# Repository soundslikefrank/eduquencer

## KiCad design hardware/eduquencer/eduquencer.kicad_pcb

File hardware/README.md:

# Eduquencer pcb schematic and design

## TODO

### Path to PCB prototype
- [ ] Finish the schematic
  - [x] Wire up rpi
  - [x] Add circuits for clock and reset
  - [x] Add debug header for flashing the rpi
  - [x] Add all the trigger jacks (+circuit around them, there might be some more resistors needed?)
  - [x] Add test-points for all i2c and SPI
  - [x] Check all GND in analog parts and change to GNDA (cv-in?)
  - [x] Annotate all parts
  - [x] Assign footprints (all footprints should be the kicad handsolder ones)
  - [ ] Add LED circuits for CV in (op-amps)
  - [ ] Adjust DAC opamp resistor for proper range (+add DAC out jack)
- [ ] Preliminary layout with all components (only footprint placement)
- [ ] Decide on a name
- [ ] Decide which jacks to use
- [ ] Do the final layout

## Preliminary BOM (per board)
- 1x RPI Pico (3,90)
- 3x https://www.digikey.de/de/products/detail/epcos-tdk-electronics/B72500D0160H060/1589537?s=N4IgTCBcDaIEIHYwFYAMqAiqCMA2VAEqviALoC%2BQA (1,5 @ 100)
- 1x GET AT JLC https://www.digikey.de/en/products/detail/texas-instruments/LM1117MP-5-0-NOPB/363590 (1,3 @ 25)
- 1x https://www.digikey.de/en/products/detail/analog-devices-inc/ADP150AUJZ-3-0-R7/2207488 (1 @ 25)
- 2x https://www.digikey.de/en/products/detail/microchip-technology/MCP23018-E-SS/1999506 (1,5 @ 25)
- 1x https://www.digikey.de/en/products/detail/texas-instruments/DAC80501MDGSR/11308813 (we probably want to get more) (5,6 @ 10)
- 2x 22u electrolytic cap (~0,5 total?)
- 9x XZM2CRK45WT-9 (red)
- 10x: XZDGK45WT-9 (green)
- 16x switches (~16 total?)
- 1x https://www.digikey.de/en/products/detail/texas-instruments/TL074CD/277422 (1 @ 25)
- 1x GET AT JLCPCB https://www.digikey.de/en/products/detail/microchip-technology/MCP6002-E-MS/683195 (0,4 @ 25)
- 1x https://www.digikey.com.au/en/products/detail/texas-instruments/OPA172IDR/4695363 (2,1 @ 25)
- 1x https://www.digikey.de/en/products/detail/texas-instruments/LM4040DIM3-10-0-NOPB/305141 (0,6 @ 25)
- 1x https://www.digikey.de/en/products/detail/texas-instruments/LM4040DIM3-5-0-NOPB/305140 (0,6 @ 25)
- 1x https://www.digikey.de/en/products/detail/panjit-international-inc/MMBT3904W-R1-00001/14660622 (0,15 @ 10)
- 3x GET AT JLC https://www.digikey.de/en/products/detail/diodes-incorporated/1N5819HWQ-7-F/10294862
- 1x GET AT JLC https://www.digikey.de/en/products/detail/panjit-international-inc/1N4148W-R1-00001/14660400
- 11x Thonkiconn (0,25 - I have ~300)
- 2x https://www.thonk.co.uk/shop/short-trimmer-pots/ B100K (0,8)

### LEDs
- MCP capabilities: 25mA sink per pin, 400mA total
- RPI capabilities: 3V3 is the main 3.3V supply to RP2040 and its I/O, generated by the on-board SMPS. This pin can be used to power external circuitry (maximum output current will depend on RP2040 load and VSYS voltage, it is recommended to keep the load on this pin less than 300mA).
- Step/channel LEDs:
  - Green: XZDGK45WT-9; 1.4mA@560Ω@3v3
  - Red: XZM2CRK45WT-9; 6.3mA@220Ω@3v3

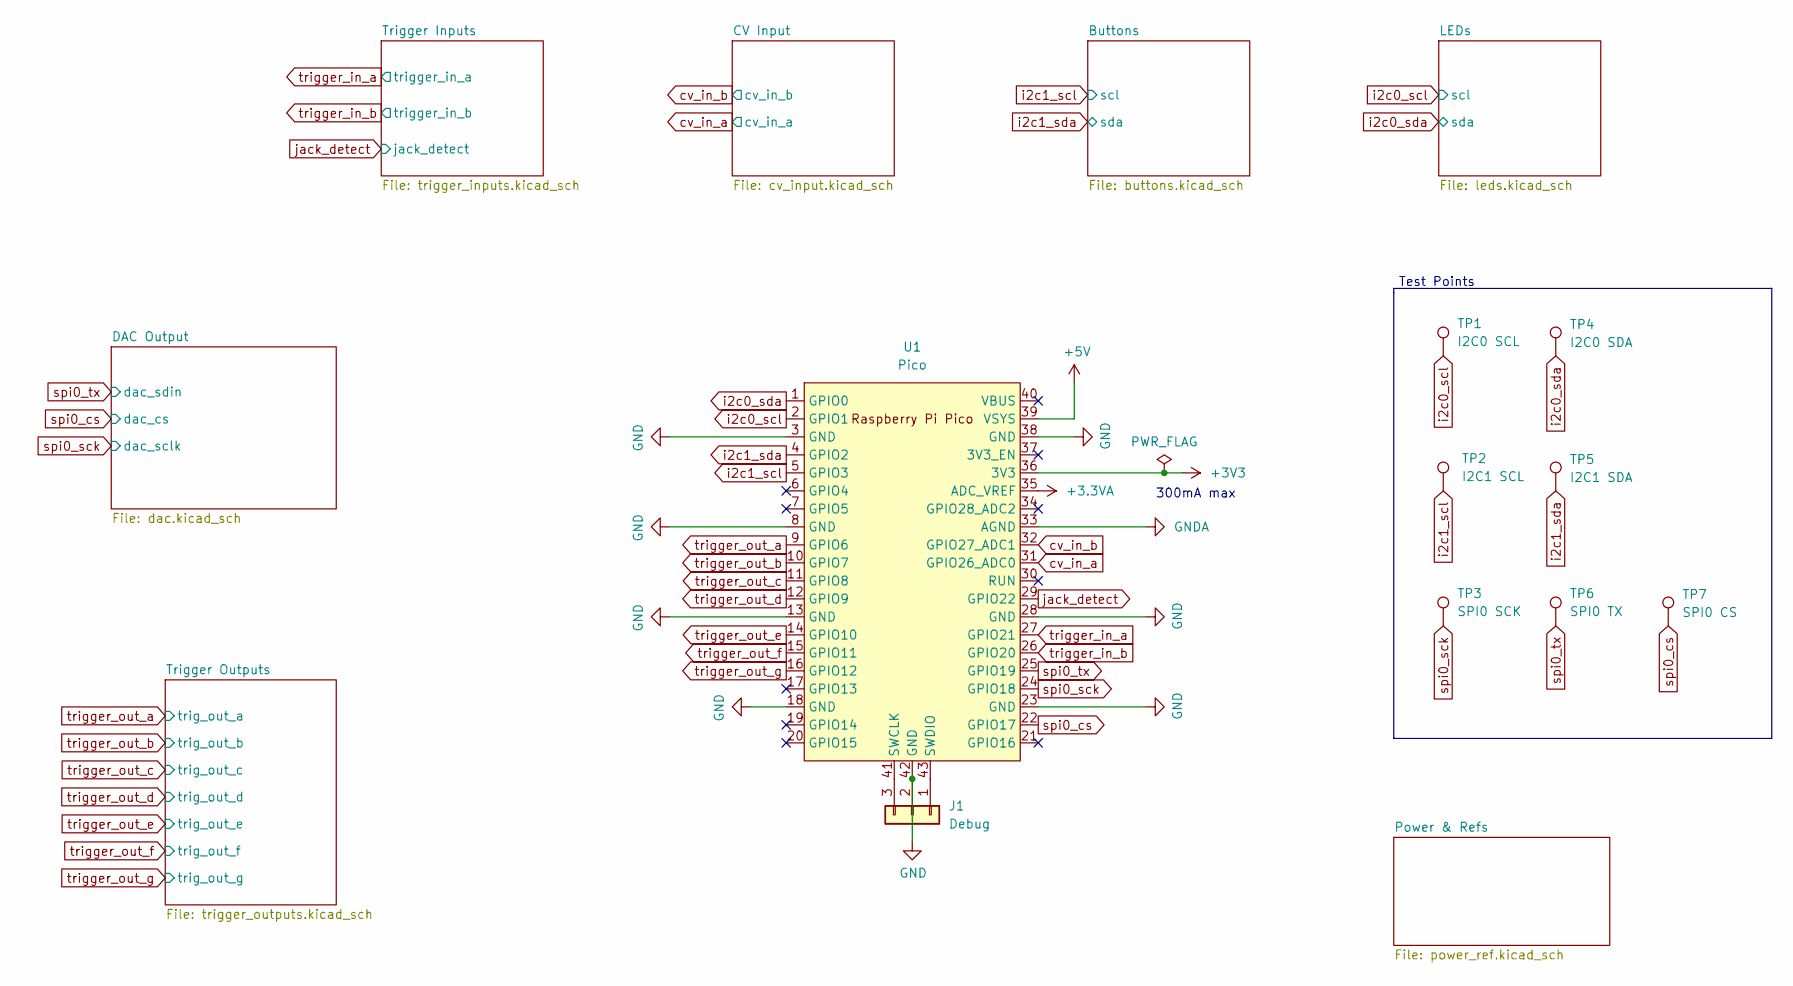
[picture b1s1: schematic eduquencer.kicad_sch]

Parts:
J1: Debug; PinHeader_1x03_P2.54mm_Vertical
TP1: I2C0 SCL; TestPoint_Pad_2.0x2.0mm
TP2: I2C1 SCL; TestPoint_Pad_2.0x2.0mm
TP3: SPI0 SCK; TestPoint_Pad_2.0x2.0mm
TP4: I2C0 SDA; TestPoint_Pad_2.0x2.0mm
TP5: I2C1 SDA; TestPoint_Pad_2.0x2.0mm
TP6: SPI0 TX; TestPoint_Pad_2.0x2.0mm
TP7: SPI0 CS; TestPoint_Pad_2.0x2.0mm
U1: Pico; RPi_Pico_SMD_TH

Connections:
+3.3VA: U1.35 (ADC_VREF); also elsewhere on the board
+5V: U1.39 (VSYS); also elsewhere on the board
GND: J1.2, U1.3 (GND), U1.8 (GND), U1.13 (GND), U1.18 (GND), U1.23 (GND), U1.28 (GND), U1.38 (GND), U1.42 (GND); also elsewhere on the board
GNDA: U1.33 (AGND); also elsewhere on the board
unnamed: J1.1, U1.43 (SWDIO)
unnamed: J1.3, U1.41 (SWCLK)
cv_in_a: U1.31 (GPIO26_ADC0); also elsewhere on the board
cv_in_b: U1.32 (GPIO27_ADC1); also elsewhere on the board
i2c0_scl: TP1.1, U1.2 (GPIO1); also elsewhere on the board
i2c0_sda: TP4.1, U1.1 (GPIO0); also elsewhere on the board
i2c1_scl: TP2.1, U1.5 (GPIO3); also elsewhere on the board
i2c1_sda: TP5.1, U1.4 (GPIO2); also elsewhere on the board
jack_detect: U1.29 (GPIO22); also elsewhere on the board
spi0_cs: TP7.1, U1.22 (GPIO17); also elsewhere on the board
spi0_sck: TP3.1, U1.24 (GPIO18); also elsewhere on the board
spi0_tx: TP6.1, U1.25 (GPIO19); also elsewhere on the board
trigger_in_a: U1.27 (GPIO21); also elsewhere on the board
trigger_in_b: U1.26 (GPIO20); also elsewhere on the board
trigger_out_a: U1.9 (GPIO6); also elsewhere on the board
trigger_out_b: U1.10 (GPIO7); also elsewhere on the board
trigger_out_c: U1.11 (GPIO8); also elsewhere on the board
trigger_out_d: U1.12 (GPIO9); also elsewhere on the board
trigger_out_e: U1.14 (GPIO10); also elsewhere on the board
trigger_out_f: U1.15 (GPIO11); also elsewhere on the board
trigger_out_g: U1.16 (GPIO12); also elsewhere on the board

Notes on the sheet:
300mA max
Test Points

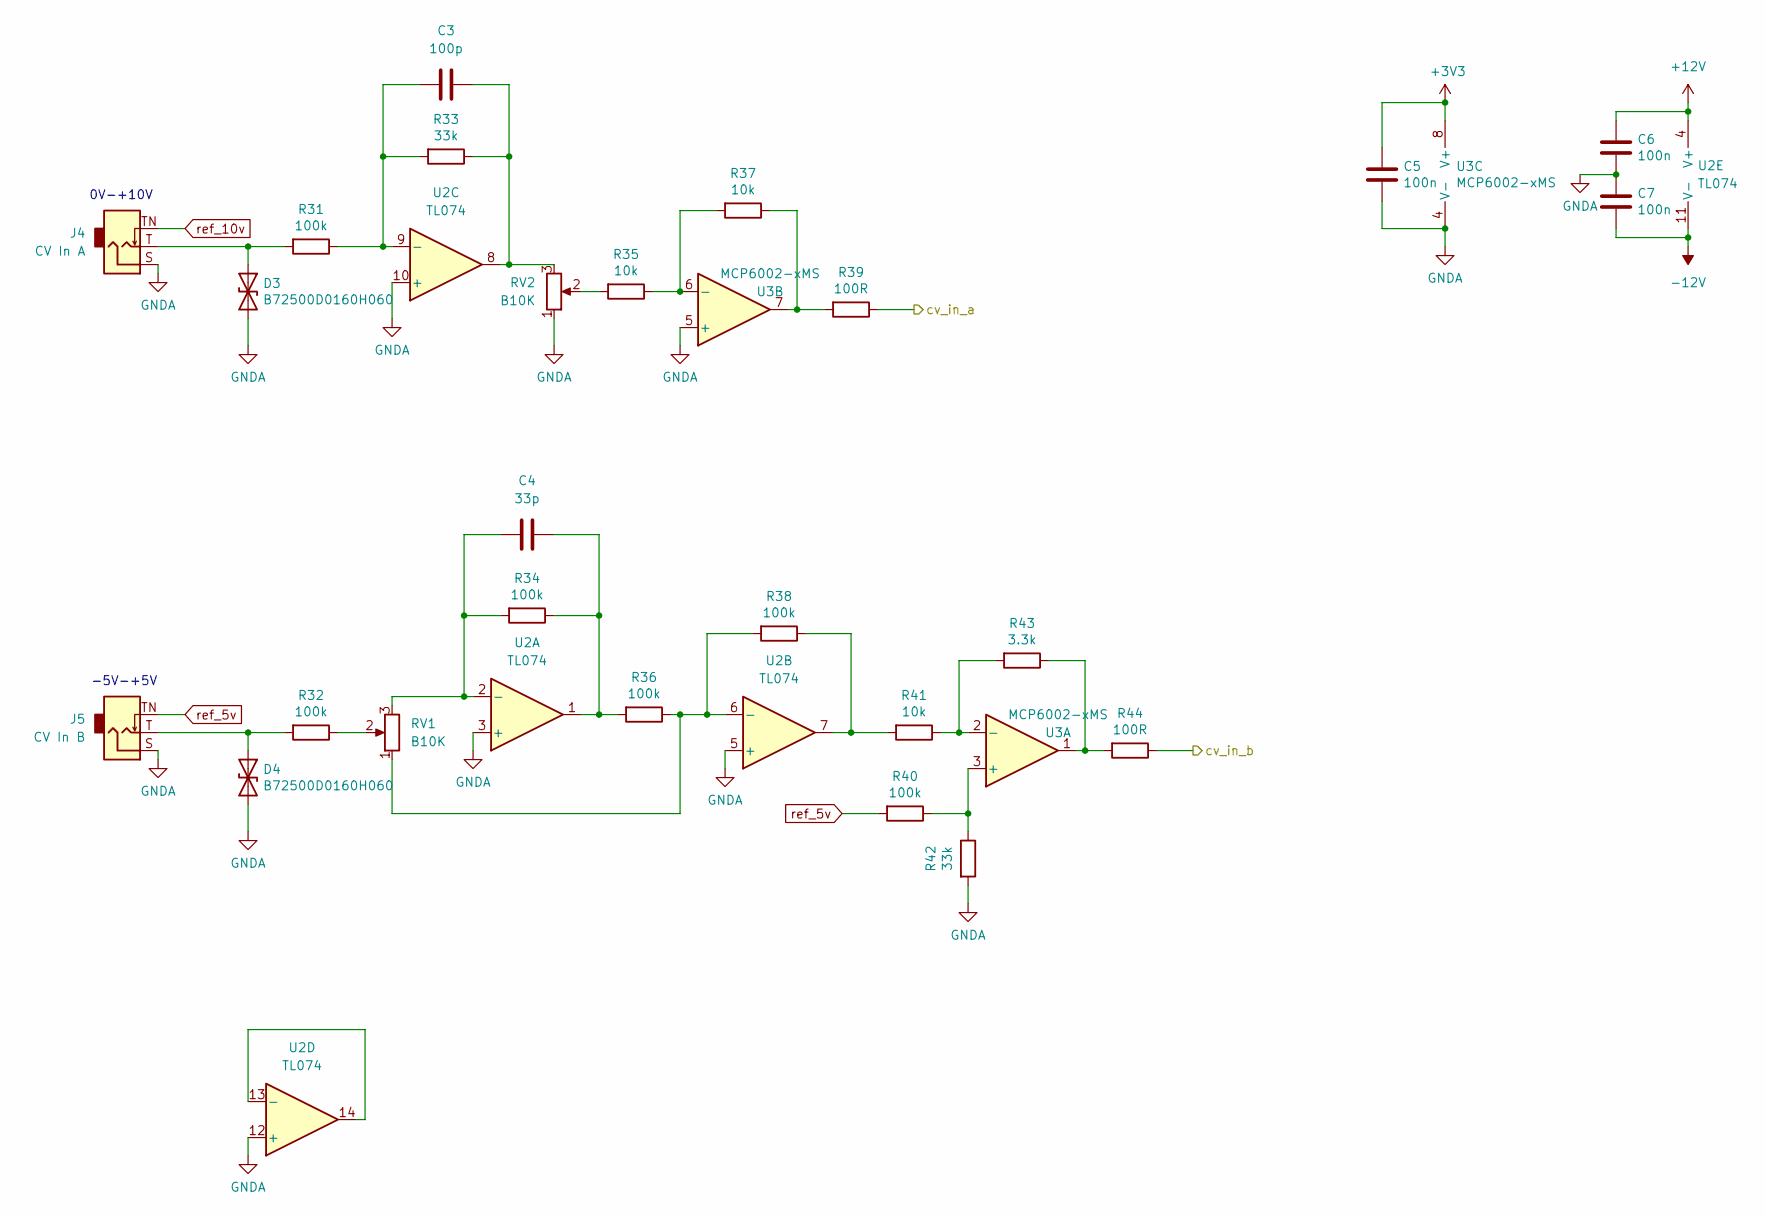
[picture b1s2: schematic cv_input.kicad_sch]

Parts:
C3: 100p; C_0603_1608Metric_Pad1.08x0.95mm_HandSolder
C4: 33p; C_0603_1608Metric_Pad1.08x0.95mm_HandSolder
C5, C6, C7: 100n; C_0603_1608Metric_Pad1.08x0.95mm_HandSolder
D3, D4: B72500D0160H060; D_0603_1608Metric_Pad1.05x0.95mm_HandSolder
J4: CV In A; Jack_3.5mm_QingPu_WQP-PJ301BM_Vertical
J5: CV In B; Jack_3.5mm_QingPu_WQP-PJ301BM_Vertical
R31, R32, R34, R36, R38, R40: 100k; R_0603_1608Metric_Pad0.98x0.95mm_HandSolder
R33, R42: 33k; R_0603_1608Metric_Pad0.98x0.95mm_HandSolder
R35, R37, R41: 10k; R_0603_1608Metric_Pad0.98x0.95mm_HandSolder
R39, R44: 100R; R_0603_1608Metric_Pad0.98x0.95mm_HandSolder
R43: 3.3k; R_0603_1608Metric_Pad0.98x0.95mm_HandSolder
RV1, RV2: B10K; Potentiometer_Alpha_RD901F-40-00D_Single_Vertical
U2: TL074; SOIC-14_3.9x8.7mm_P1.27mm
U3: MCP6002-xMS; SOIC-8_3.9x4.9mm_P1.27mm

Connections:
+12V: C6.1, U2.4 (V+); also elsewhere on the board
-12V: C7.2, U2.11 (V-); also elsewhere on the board
GNDA: C5.2, C6.2, C7.1, D3.2 (A2), D4.2 (A2), J4.S, J5.S, R42.2, RV2.1, U2.3 (+), U2.5 (+), U2.10 (+), U2.12 (+), U3.4 (V-), U3.5 (+); also elsewhere on the board
unnamed: C3.1, R31.1, R33.2, U2.9 (-)
unnamed: C3.2, R33.1, RV2.3, U2.8
unnamed: C4.1, R34.2, RV1.3, U2.2 (-)
unnamed: C4.2, R34.1, R36.2, U2.1
unnamed: D3.1 (A1), J4.T, R31.2
unnamed: D4.1 (A1), J5.T, R32.2
unnamed: R32.1, RV1.2
unnamed: R35.1, R37.2, U3.6 (-)
unnamed: R35.2, RV2.2
unnamed: R36.1, R38.2, RV1.1, U2.6 (-)
unnamed: R37.1, R39.2, U3.7
unnamed: R38.1, R41.2, U2.7
unnamed: R40.1, R42.1, U3.3 (+)
unnamed: R41.1, R43.2, U3.2 (-)
unnamed: R43.1, R44.2, U3.1
unnamed: U2.13 (-), U2.14
cv_in_a: R39.1; also elsewhere on the board
cv_in_b: R44.1; also elsewhere on the board
ref_5v: J5.TN, R40.2; also elsewhere on the board
ref_10v: J4.TN; also elsewhere on the board

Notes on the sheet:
0V-+10V
-5V-+5V

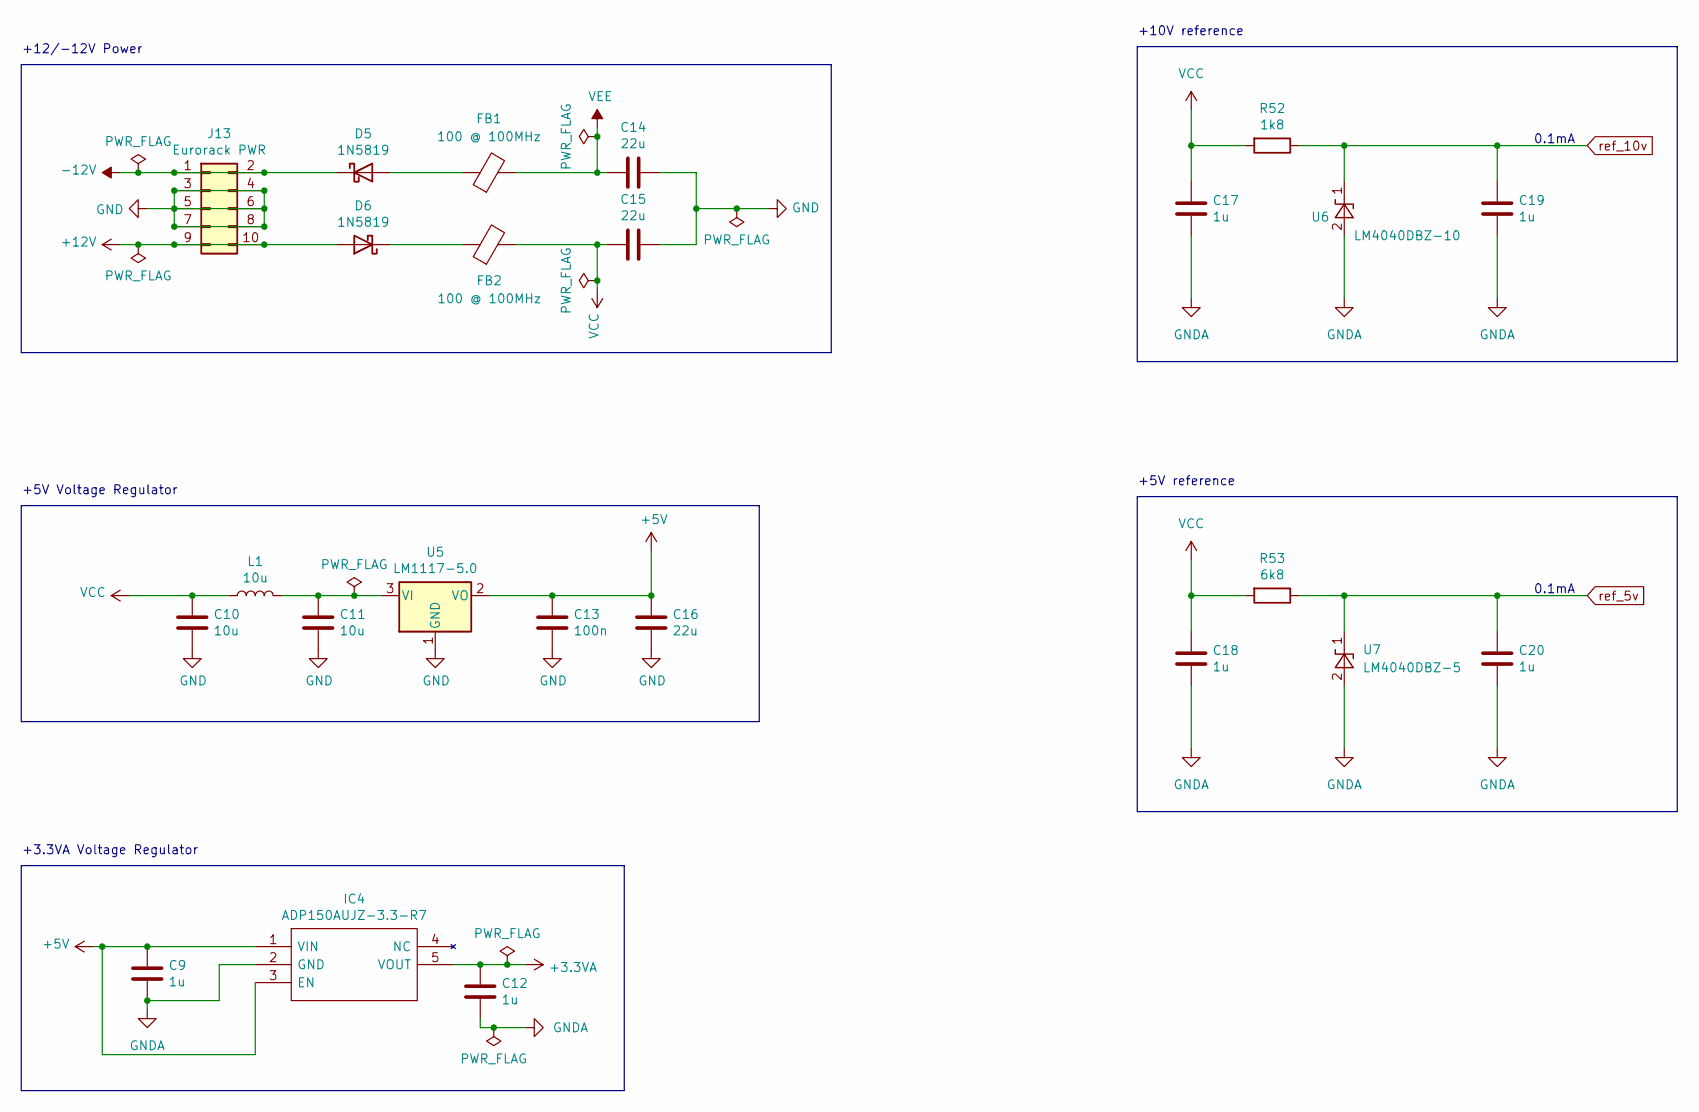
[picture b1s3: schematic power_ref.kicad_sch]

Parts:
C9, C12, C17, C18, C19, C20: 1u; C_0603_1608Metric_Pad1.08x0.95mm_HandSolder
C10, C11: 10u; C_0805_2012Metric_Pad1.18x1.45mm_HandSolder
C13: 100n; C_0603_1608Metric_Pad1.08x0.95mm_HandSolder
C14, C15: 22u; CP_Elec_5x5.3
C16: 22u; C_0805_2012Metric_Pad1.18x1.45mm_HandSolder
D5, D6: 1N5819; D_SOD-123
FB1, FB2: 100 @ 100MHz; L_0805_2012Metric_Pad1.05x1.20mm_HandSolder
IC4: ADP150AUJZ-3.3-R7; SOT95P280X100-5N; Manufacturer_Part_Number ADP150AUJZ-3.3-R7; Mouser Part Number 584-ADP150AUJZ-3.3R7
J13: Eurorack PWR; PinHeader_2x05_P2.54mm_Vertical_SMD
L1: 10u; L_0805_2012Metric_Pad1.05x1.20mm_HandSolder
R52: 1k8; R_0603_1608Metric_Pad0.98x0.95mm_HandSolder
R53: 6k8; R_0603_1608Metric_Pad0.98x0.95mm_HandSolder
U5: LM1117-5.0; SOT-223
U6: LM4040DBZ-10; SOT-23_Handsoldering
U7: LM4040DBZ-5; SOT-23_Handsoldering

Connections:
+3.3VA: C12.1, IC4.5 (VOUT); also elsewhere on the board
+5V: C9.1, C13.1, C16.2, IC4.1 (VIN), IC4.3 (EN), U5.2 (VO); also elsewhere on the board
+12V: D6.2 (A), J13.9, J13.10; also elsewhere on the board
-12V: D5.1 (K), J13.1, J13.2; also elsewhere on the board
GND: C10.2, C11.1, C13.2, C14.1, C15.1, C16.1, J13.3, J13.4, J13.5, J13.6, J13.7, J13.8, U5.1 (GND); also elsewhere on the board
GNDA: C9.2, C12.2, C17.2, C18.2, C19.2, C20.2, IC4.2 (GND), U6.2 (A), U7.2 (A); also elsewhere on the board
unnamed: C11.2, L1.2, U5.3 (VI)
unnamed: D5.2 (A), FB1.1
unnamed: D6.1 (K), FB2.1
VCC: C10.1, C15.2, C17.1, C18.1, FB2.2, L1.1, R52.2, R53.2; also elsewhere on the board
VEE: C14.2, FB1.2; also elsewhere on the board
ref_5v: C20.1, R53.1, U7.1 (K); also elsewhere on the board
ref_10v: C19.1, R52.1, U6.1 (K); also elsewhere on the board

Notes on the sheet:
+5V Voltage Regulator
0.1mA
+3.3VA Voltage Regulator
+12/-12V Power
+10V reference
+5V reference

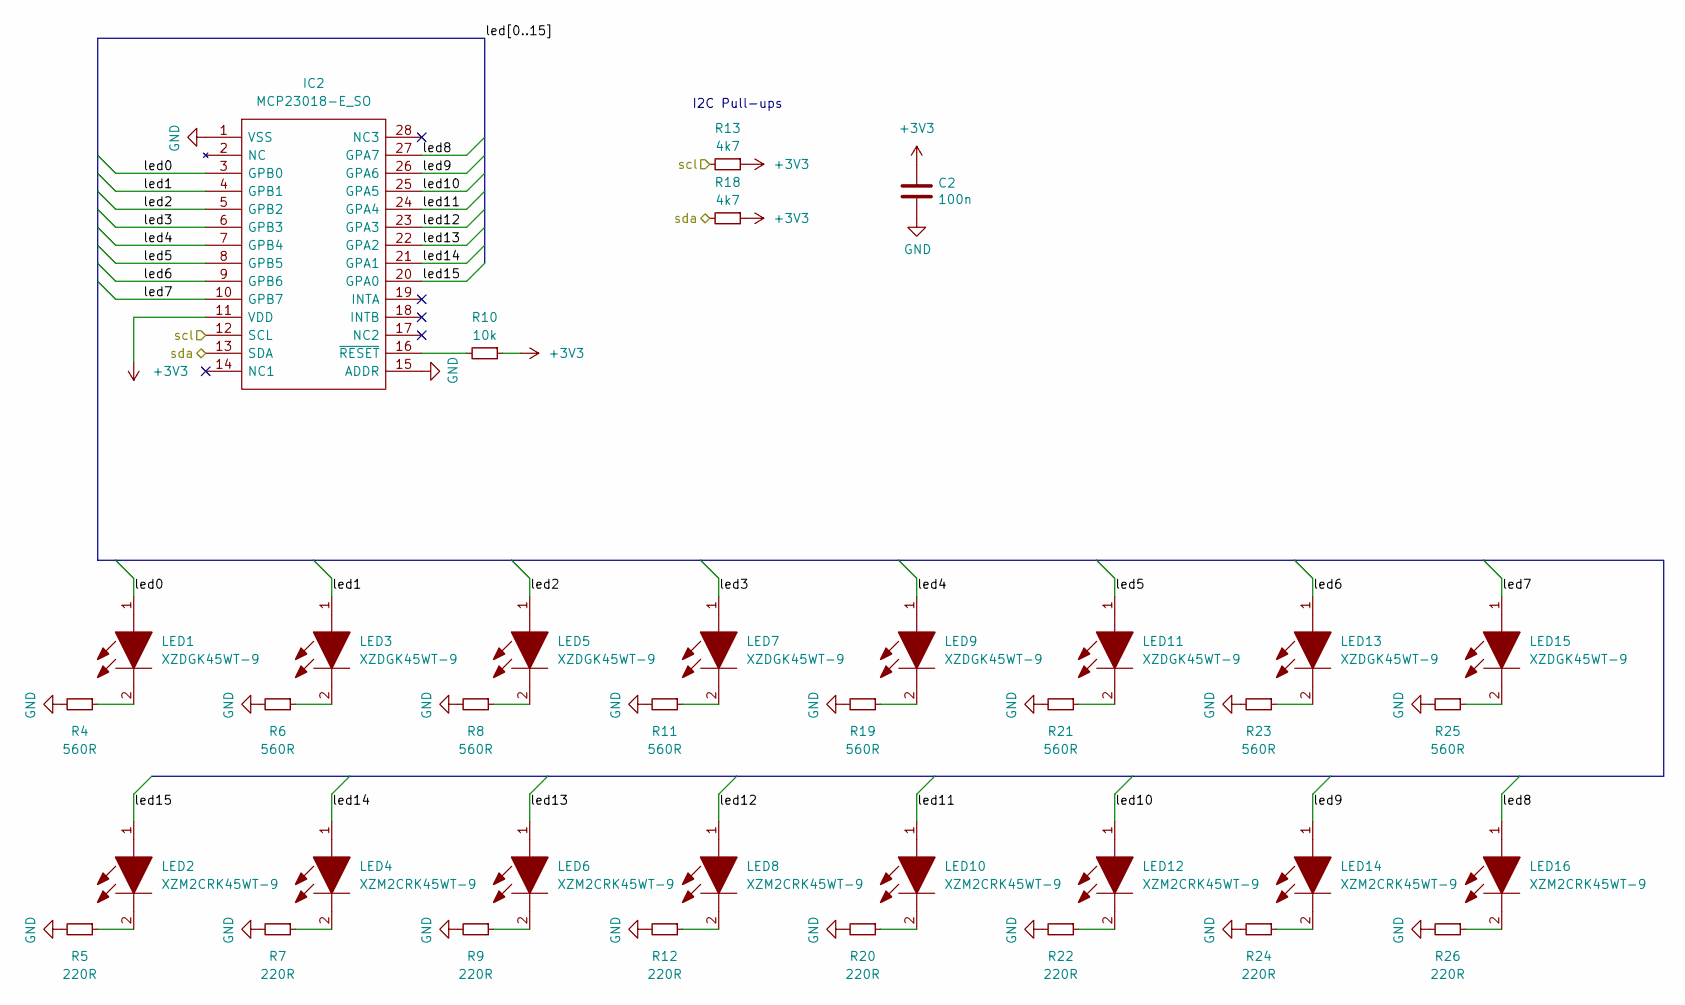
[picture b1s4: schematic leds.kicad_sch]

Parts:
C2: 100n; C_0603_1608Metric_Pad1.08x0.95mm_HandSolder
IC2: MCP23018-E_SO; SOIC127P1030X265-28N; Manufacturer_Part_Number MCP23018-E/SO; Mouser Part Number 579-MCP23018-E/SO
LED1, LED3, LED5, LED7, LED9, LED11, LED13, LED15: XZDGK45WT-9; XZMYK45WT9; Manufacturer_Part_Number XZMYK45WT-9
LED2, LED4, LED6, LED8, LED10, LED12, LED14, LED16: XZM2CRK45WT-9; XZMYK45WT9; Manufacturer_Part_Number XZMYK45WT-9
R4, R6, R8, R11, R19, R21, R23, R25: 560R; R_0603_1608Metric_Pad0.98x0.95mm_HandSolder
R5, R7, R9, R12, R20, R22, R24, R26: 220R; R_0603_1608Metric_Pad0.98x0.95mm_HandSolder
R10: 10k; R_0603_1608Metric_Pad0.98x0.95mm_HandSolder
R13, R18: 4k7; R_0603_1608Metric_Pad0.98x0.95mm_HandSolder

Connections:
/LEDs/led0: IC2.3 (GPB0), LED1.1
/LEDs/led1: IC2.4 (GPB1), LED3.1
/LEDs/led2: IC2.5 (GPB2), LED5.1
/LEDs/led3: IC2.6 (GPB3), LED7.1
/LEDs/led4: IC2.7 (GPB4), LED9.1
/LEDs/led5: IC2.8 (GPB5), LED11.1
/LEDs/led6: IC2.9 (GPB6), LED13.1
/LEDs/led7: IC2.10 (GPB7), LED15.1
/LEDs/led8: IC2.27 (GPA7), LED16.1
/LEDs/led9: IC2.26 (GPA6), LED14.1
/LEDs/led10: IC2.25 (GPA5), LED12.1
/LEDs/led11: IC2.24 (GPA4), LED10.1
/LEDs/led12: IC2.23 (GPA3), LED8.1
/LEDs/led13: IC2.22 (GPA2), LED6.1
/LEDs/led14: IC2.21 (GPA1), LED4.1
/LEDs/led15: IC2.20 (GPA0), LED2.1
GND: C2.2, IC2.1 (VSS), IC2.15 (ADDR), R4.2, R5.2, R6.2, R7.2, R8.2, R9.2, R11.2, R12.2, R19.2, R20.2, R21.2, R22.2, R23.2, R24.2, R25.2, R26.2; also elsewhere on the board
unnamed: IC2.16 (~RESET), R10.2
unnamed: LED1.2, R4.1
unnamed: LED2.2, R5.1
unnamed: LED3.2, R6.1
unnamed: LED4.2, R7.1
unnamed: LED5.2, R8.1
unnamed: LED6.2, R9.1
unnamed: LED7.2, R11.1
unnamed: LED8.2, R12.1
unnamed: LED9.2, R19.1
unnamed: LED10.2, R20.1
unnamed: LED11.2, R21.1
unnamed: LED12.2, R22.1
unnamed: LED13.2, R23.1
unnamed: LED14.2, R24.1
unnamed: LED15.2, R25.1
unnamed: LED16.2, R26.1
i2c0_scl: IC2.12 (SCL), R13.2; also elsewhere on the board
i2c0_sda: IC2.13 (SDA), R18.2; also elsewhere on the board

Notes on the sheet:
I2C Pull-ups

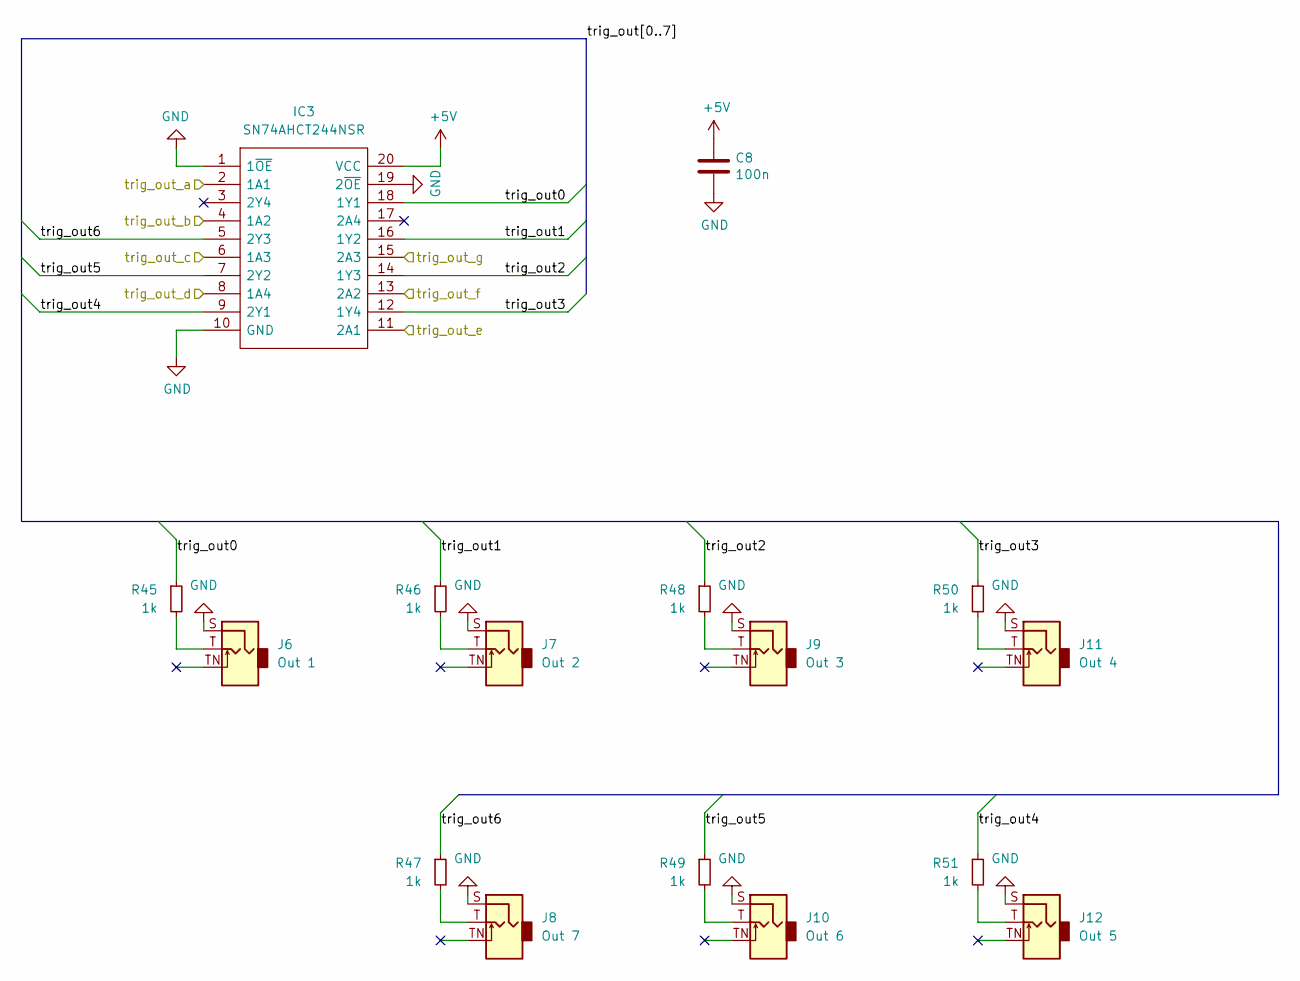
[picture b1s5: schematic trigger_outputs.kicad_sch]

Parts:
C8: 100n; C_0603_1608Metric_Pad1.08x0.95mm_HandSolder
IC3: SN74AHCT244NSR; SOIC127P780X200-20N; Manufacturer_Part_Number SN74AHCT244NSR; Mouser Part Number 595-SN74AHCT244NSR
J6: Out 1; Jack_3.5mm_QingPu_WQP-PJ301BM_Vertical
J7: Out 2; Jack_3.5mm_QingPu_WQP-PJ301BM_Vertical
J8: Out 7; Jack_3.5mm_QingPu_WQP-PJ301BM_Vertical
J9: Out 3; Jack_3.5mm_QingPu_WQP-PJ301BM_Vertical
J10: Out 6; Jack_3.5mm_QingPu_WQP-PJ301BM_Vertical
J11: Out 4; Jack_3.5mm_QingPu_WQP-PJ301BM_Vertical
J12: Out 5; Jack_3.5mm_QingPu_WQP-PJ301BM_Vertical
R45, R46, R47, R48, R49, R50, R51: 1k; R_0603_1608Metric_Pad0.98x0.95mm_HandSolder

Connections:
+5V: C8.1, IC3.20 (VCC); also elsewhere on the board
/Trigger Outputs/trig_out0: IC3.18 (1Y1), R45.1
/Trigger Outputs/trig_out1: IC3.16 (1Y2), R46.1
/Trigger Outputs/trig_out2: IC3.14 (1Y3), R48.1
/Trigger Outputs/trig_out3: IC3.12 (1Y4), R50.1
/Trigger Outputs/trig_out4: IC3.9 (2Y1), R51.1
/Trigger Outputs/trig_out5: IC3.7 (2Y2), R49.1
/Trigger Outputs/trig_out6: IC3.5 (2Y3), R47.1
GND: C8.2, IC3.1 (1~OE), IC3.10 (GND), IC3.19 (2~OE), J6.S, J7.S, J8.S, J9.S, J10.S, J11.S, J12.S; also elsewhere on the board
unnamed: J6.T, R45.2
unnamed: J7.T, R46.2
unnamed: J8.T, R47.2
unnamed: J9.T, R48.2
unnamed: J10.T, R49.2
unnamed: J11.T, R50.2
unnamed: J12.T, R51.2
trigger_out_a: IC3.2 (1A1); also elsewhere on the board
trigger_out_b: IC3.4 (1A2); also elsewhere on the board
trigger_out_c: IC3.6 (1A3); also elsewhere on the board
trigger_out_d: IC3.8 (1A4); also elsewhere on the board
trigger_out_e: IC3.11 (2A1); also elsewhere on the board
trigger_out_f: IC3.13 (2A2); also elsewhere on the board
trigger_out_g: IC3.15 (2A3); also elsewhere on the board

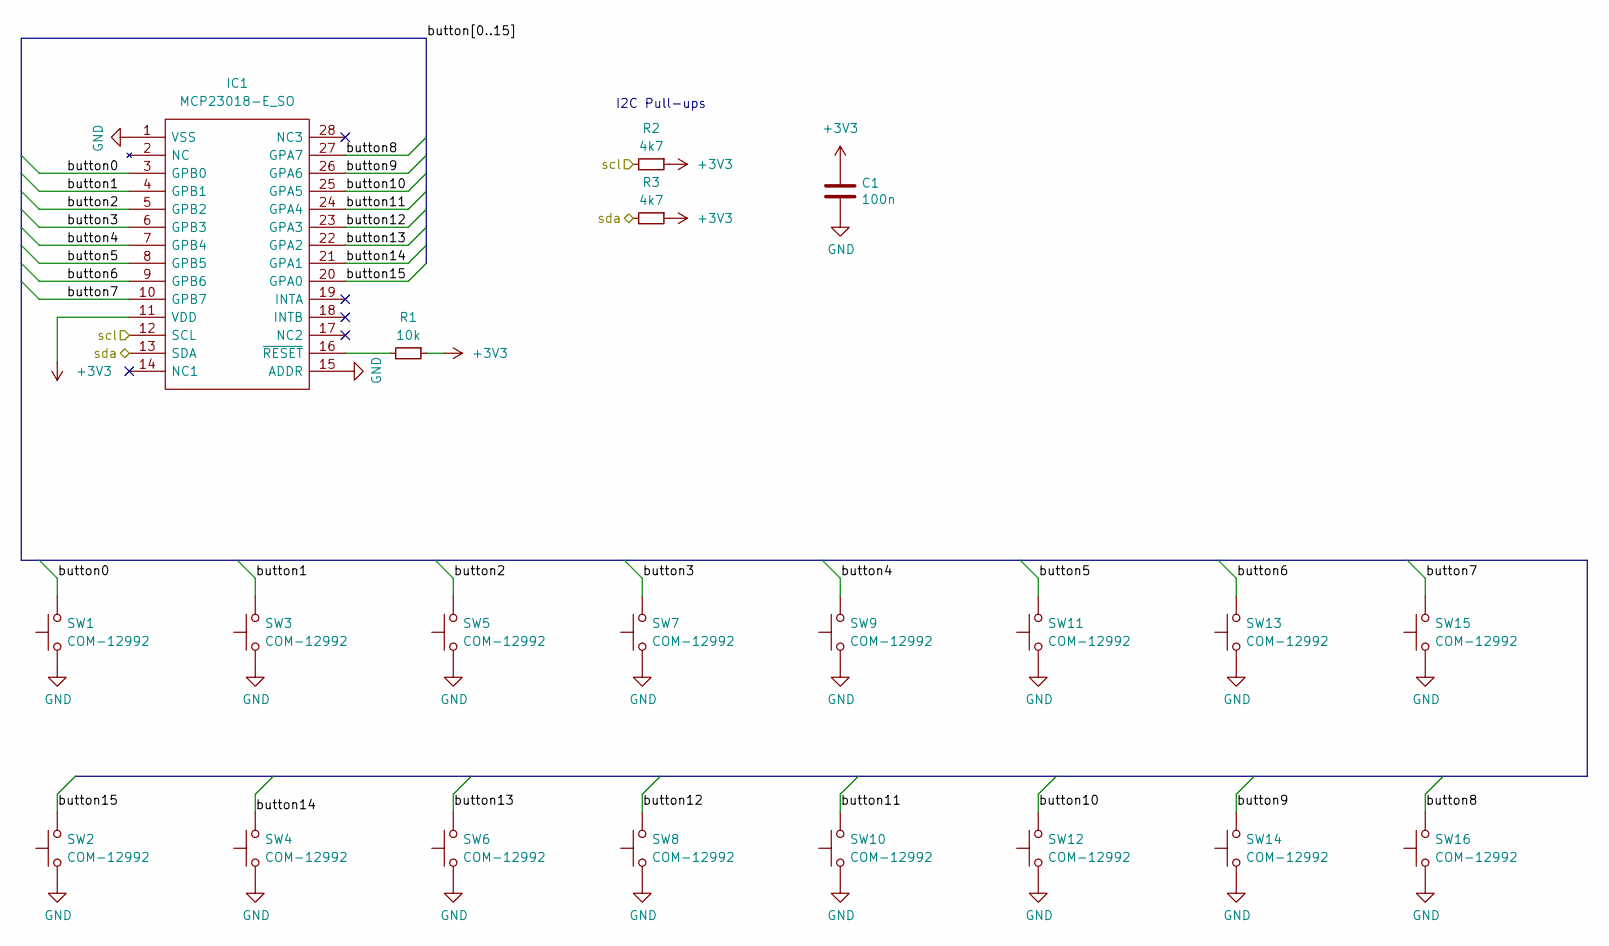
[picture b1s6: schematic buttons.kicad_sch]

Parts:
C1: 100n; C_0603_1608Metric_Pad1.08x0.95mm_HandSolder
IC1: MCP23018-E_SO; SOIC127P1030X265-28N; Manufacturer_Part_Number MCP23018-E/SO; Mouser Part Number 579-MCP23018-E/SO
R1: 10k; R_0603_1608Metric_Pad0.98x0.95mm_HandSolder
R2, R3: 4k7; R_0603_1608Metric_Pad0.98x0.95mm_HandSolder
SW1, SW2, SW3, SW4, SW5, SW6, SW7, SW8, SW9, SW10, SW11, SW12, SW13, SW14, SW15, SW16: COM-12992; SW_Push_1P1T_NO_6x6mm_H9.5mm

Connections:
/Buttons/button0: IC1.3 (GPB0), SW1.2
/Buttons/button1: IC1.4 (GPB1), SW3.2
/Buttons/button2: IC1.5 (GPB2), SW5.2
/Buttons/button3: IC1.6 (GPB3), SW7.2
/Buttons/button4: IC1.7 (GPB4), SW9.2
/Buttons/button5: IC1.8 (GPB5), SW11.2
/Buttons/button6: IC1.9 (GPB6), SW13.2
/Buttons/button7: IC1.10 (GPB7), SW15.2
/Buttons/button8: IC1.27 (GPA7), SW16.2
/Buttons/button9: IC1.26 (GPA6), SW14.2
/Buttons/button10: IC1.25 (GPA5), SW12.2
/Buttons/button11: IC1.24 (GPA4), SW10.2
/Buttons/button12: IC1.23 (GPA3), SW8.2
/Buttons/button13: IC1.22 (GPA2), SW6.2
/Buttons/button14: IC1.21 (GPA1), SW4.2
/Buttons/button15: IC1.20 (GPA0), SW2.2
GND: C1.2, IC1.1 (VSS), IC1.15 (ADDR), SW1.1, SW2.1, SW3.1, SW4.1, SW5.1, SW6.1, SW7.1, SW8.1, SW9.1, SW10.1, SW11.1, SW12.1, SW13.1, SW14.1, SW15.1, SW16.1; also elsewhere on the board
unnamed: IC1.16 (~RESET), R1.2
i2c1_scl: IC1.12 (SCL), R2.2; also elsewhere on the board
i2c1_sda: IC1.13 (SDA), R3.2; also elsewhere on the board

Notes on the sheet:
I2C Pull-ups

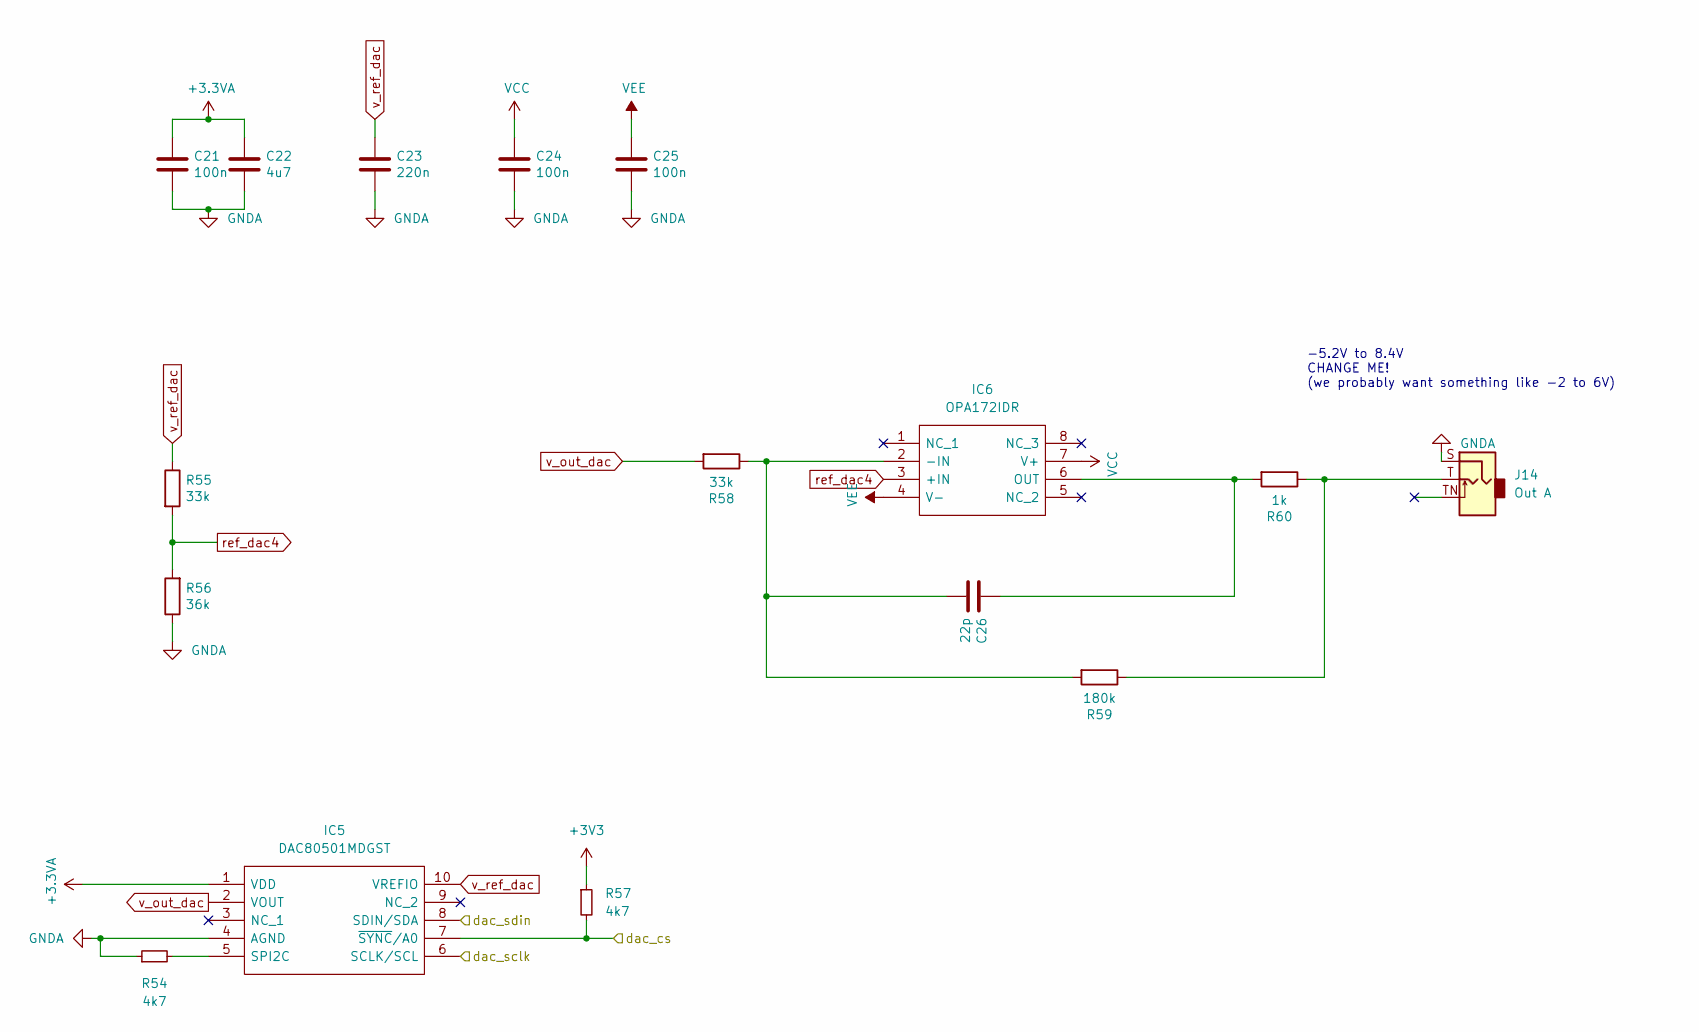
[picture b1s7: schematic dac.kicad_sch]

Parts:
C21, C24, C25: 100n; C_0603_1608Metric_Pad1.08x0.95mm_HandSolder
C22: 4u7; C_0603_1608Metric_Pad1.08x0.95mm_HandSolder
C23: 220n; C_0603_1608Metric_Pad1.08x0.95mm_HandSolder
C26: 22p; C_0603_1608Metric_Pad1.08x0.95mm_HandSolder
IC5: DAC80501MDGST; SOP50P490X110-10N; Manufacturer_Part_Number DAC80501MDGST; Mouser Part Number 595-DAC80501MDGST
IC6: OPA172IDR; SOIC127P600X175-8N; Manufacturer_Part_Number OPA172IDR; Mouser Part Number 595-OPA172IDR
J14: Out A; Jack_3.5mm_QingPu_WQP-PJ301BM_Vertical
R54, R57: 4k7; R_0603_1608Metric_Pad0.98x0.95mm_HandSolder
R55, R58: 33k; R_0603_1608Metric_Pad0.98x0.95mm_HandSolder
R56: 36k; R_0603_1608Metric_Pad0.98x0.95mm_HandSolder
R59: 180k; R_0603_1608Metric_Pad0.98x0.95mm_HandSolder
R60: 1k; R_0603_1608Metric_Pad0.98x0.95mm_HandSolder

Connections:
+3.3VA: C21.2, C22.1, IC5.1 (VDD); also elsewhere on the board
GNDA: C21.1, C22.2, C23.1, C24.1, C25.1, IC5.4 (AGND), J14.S, R54.1, R56.1; also elsewhere on the board
unnamed: C26.1, IC6.2 (-IN), R58.1, R59.2
unnamed: C26.2, IC6.6 (OUT), R60.2
unnamed: IC5.5 (SPI2C), R54.2
unnamed: J14.T, R59.1, R60.1
VCC: C24.2, IC6.7 (V+); also elsewhere on the board
VEE: C25.2, IC6.4 (V-); also elsewhere on the board
ref_dac4: IC6.3 (+IN), R55.2, R56.2
spi0_cs: IC5.7 (~SYNC/A0), R57.2; also elsewhere on the board
spi0_sck: IC5.6 (SCLK/SCL); also elsewhere on the board
spi0_tx: IC5.8 (SDIN/SDA); also elsewhere on the board
v_out_dac: IC5.2 (VOUT), R58.2
v_ref_dac: C23.2, IC5.10 (VREFIO), R55.1

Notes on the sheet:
-5.2V to 8.4V CHANGE ME! (we probably want something like -2 to 6V)

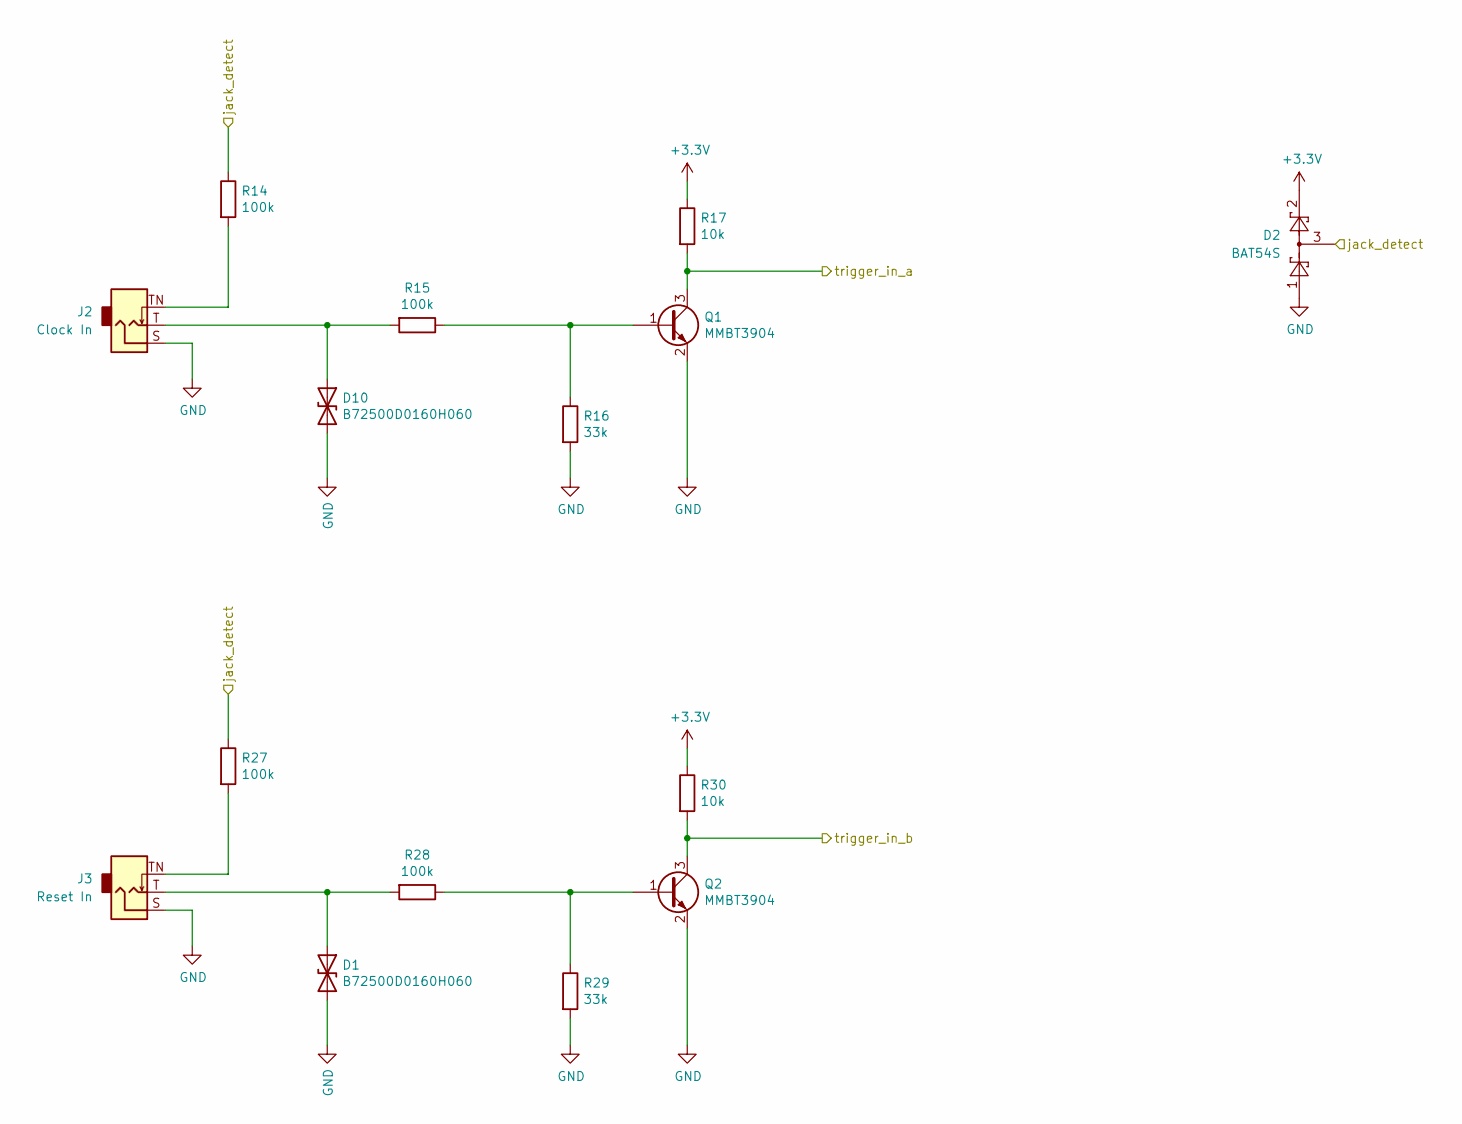
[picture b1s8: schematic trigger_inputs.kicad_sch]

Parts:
D1, D10: B72500D0160H060; D_0603_1608Metric_Pad1.05x0.95mm_HandSolder
D2: BAT54S; SOT-23_Handsoldering
J2: Clock In; Jack_3.5mm_QingPu_WQP-PJ301BM_Vertical
J3: Reset In; Jack_3.5mm_QingPu_WQP-PJ301BM_Vertical
Q1, Q2: MMBT3904; SOT-23
R14, R15, R27, R28: 100k; R_0603_1608Metric_Pad0.98x0.95mm_HandSolder
R16, R29: 33k; R_0603_1608Metric_Pad0.98x0.95mm_HandSolder
R17, R30: 10k; R_0603_1608Metric_Pad0.98x0.95mm_HandSolder

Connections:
GND: D1.2 (A2), D2.1, D10.2 (A2), J2.S, J3.S, Q1.2 (E), Q2.2 (E), R16.2, R29.2; also elsewhere on the board
unnamed: D1.1 (A1), J3.T, R28.2
unnamed: D10.1 (A1), J2.T, R15.2
unnamed: J2.TN, R14.2
unnamed: J3.TN, R27.2
unnamed: Q1.1 (B), R15.1, R16.1
unnamed: Q2.1 (B), R28.1, R29.1
jack_detect: D2.3, R14.1, R27.1; also elsewhere on the board
trigger_in_a: Q1.3 (C), R17.2; also elsewhere on the board
trigger_in_b: Q2.3 (C), R30.2; also elsewhere on the board

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
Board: 2 copper layers, 166 parts (0 on the bottom side), 128 nets, no tracks yet.

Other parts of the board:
Ref**: Val**; eduquencer-inkscape
